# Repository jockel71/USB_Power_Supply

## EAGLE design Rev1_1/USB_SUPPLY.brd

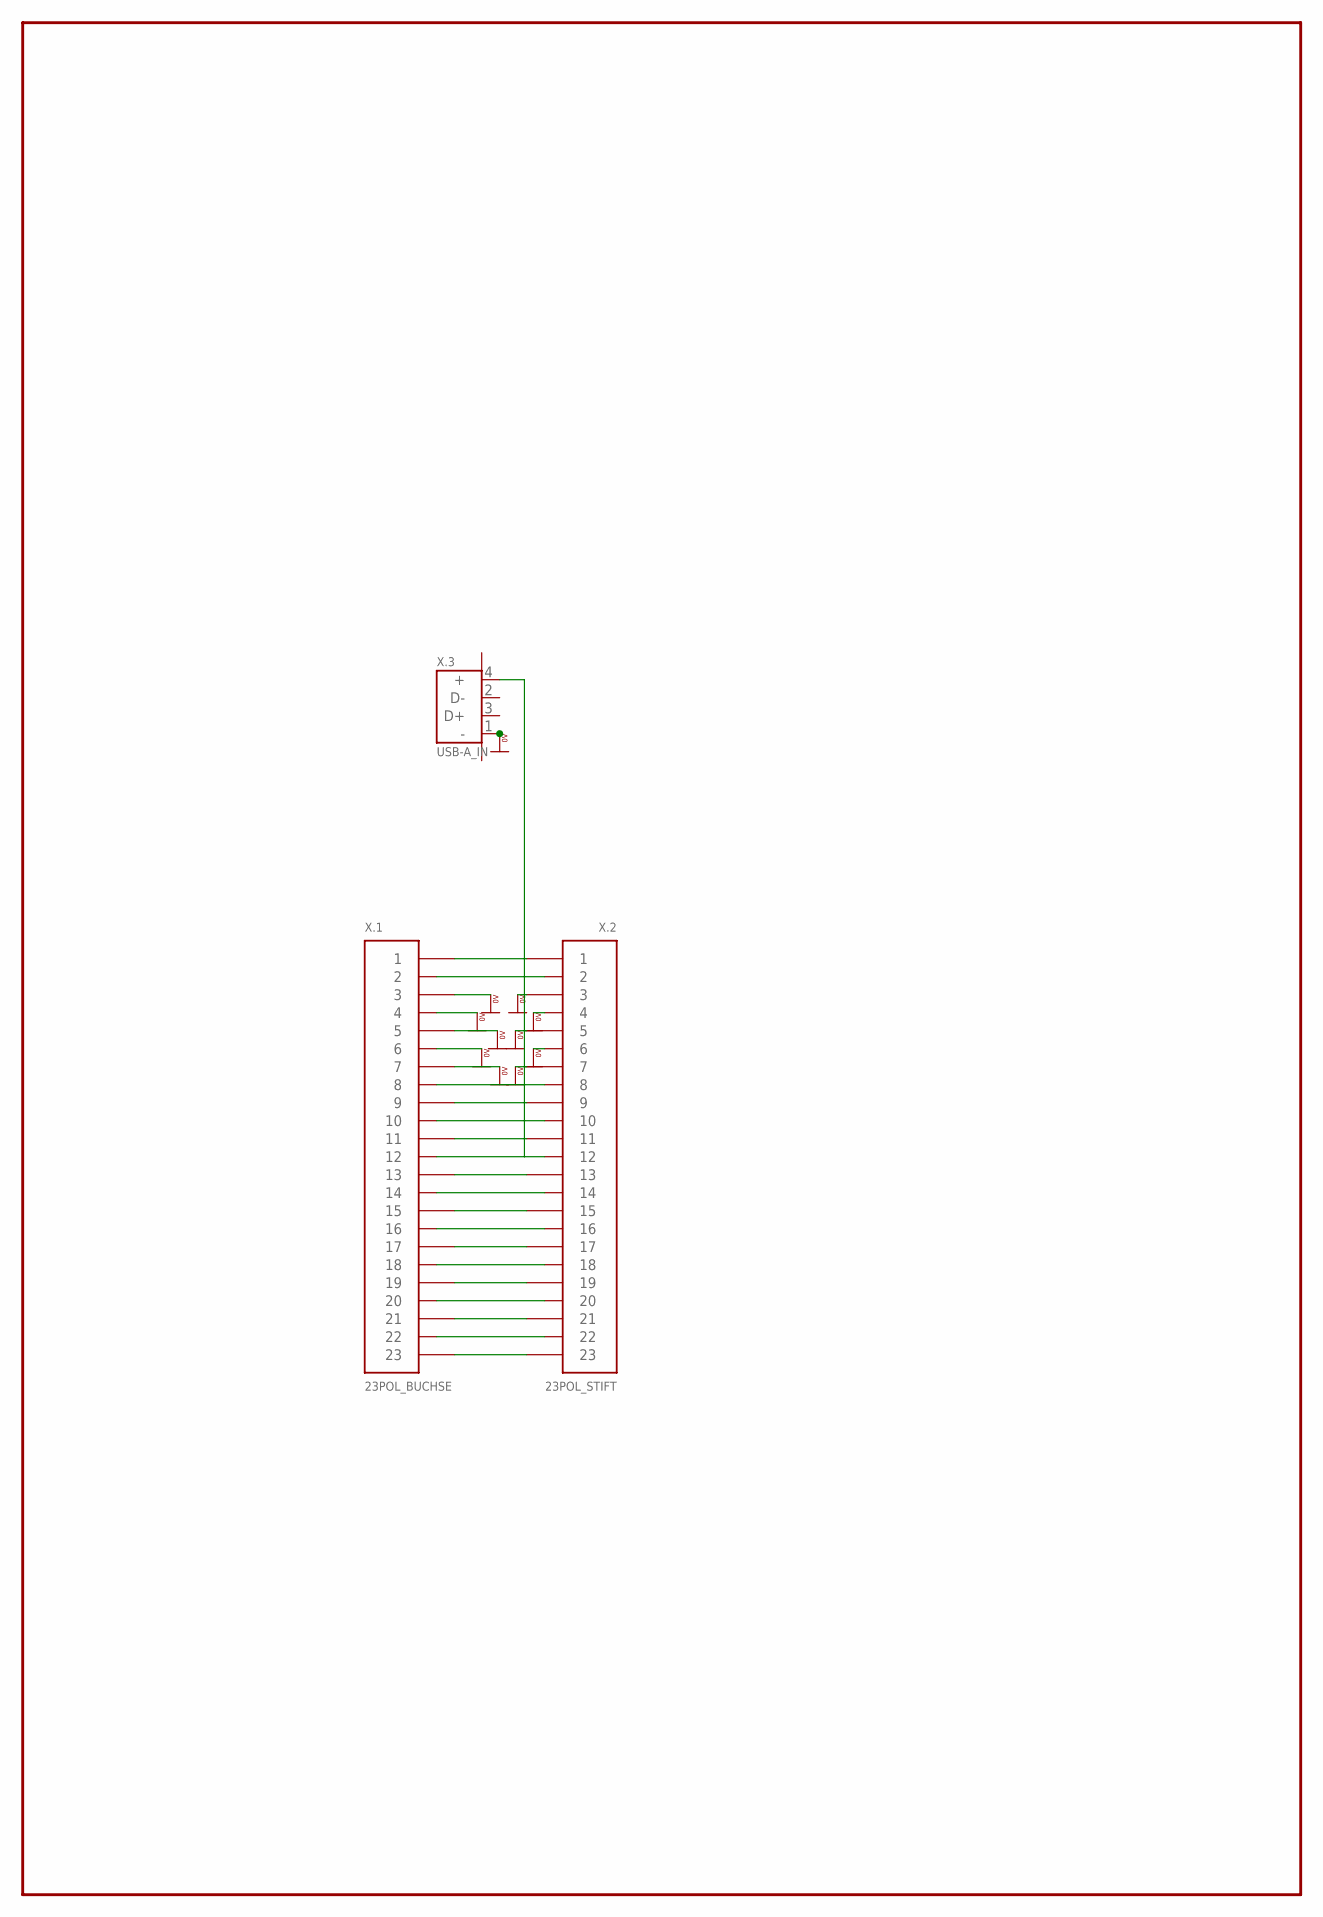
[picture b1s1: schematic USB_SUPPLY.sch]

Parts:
X.1: 23POL_BUCHSE; SUB-D_23F_L
X.2: 23POL_STIFT; SUB-D_23M_L
X.3: USB-A_IN; USB-A-90_IN

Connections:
0V: X.1.3, X.1.4, X.1.5, X.1.6, X.1.7, X.2.3, X.2.4, X.2.5, X.2.6, X.2.7, X.3.1 (-)
unnamed: X.1.1, X.2.1
unnamed: X.1.9, X.2.9
unnamed: X.1.11, X.2.11
unnamed: X.1.13, X.2.13
unnamed: X.1.15, X.2.15
unnamed: X.1.17, X.2.17
unnamed: X.1.19, X.2.19
unnamed: X.1.21, X.2.21
unnamed: X.1.23, X.2.23
unnamed: X.1.2, X.2.2
unnamed: X.1.8, X.2.8
unnamed: X.1.10, X.2.10
unnamed: X.1.12, X.2.12, X.3.4 (+)
unnamed: X.1.14, X.2.14
unnamed: X.1.16, X.2.16
unnamed: X.1.18, X.2.18
unnamed: X.1.20, X.2.20
unnamed: X.1.22, X.2.22

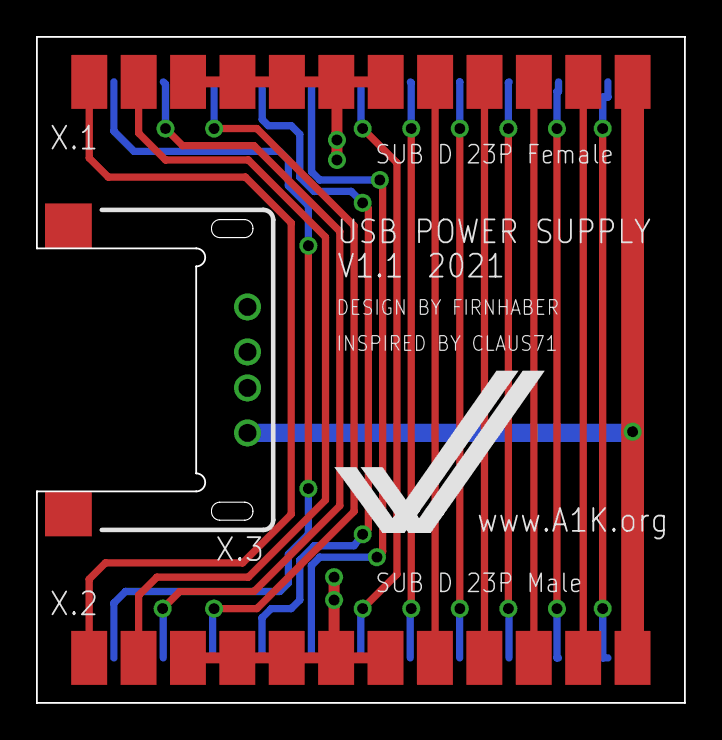
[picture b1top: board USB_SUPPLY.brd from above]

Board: 2 copper layers, 36.0 x 37.0 mm, 3 parts (0 on the bottom side), 19 nets.
